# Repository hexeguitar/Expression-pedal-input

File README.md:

# Expression-pedal-input
Work in progress, HW design for an universal expression pedal input

Link to thread at Teensy Forum:
https://forum.pjrc.com/index.php?threads/universal-midi-expression-pedal.76457/

[Html BOM](https://hexeguitar.github.io/Expression-pedal-input/KiCad_project/bom/ExpIn_3_2025-02-24.html "Html BOM")

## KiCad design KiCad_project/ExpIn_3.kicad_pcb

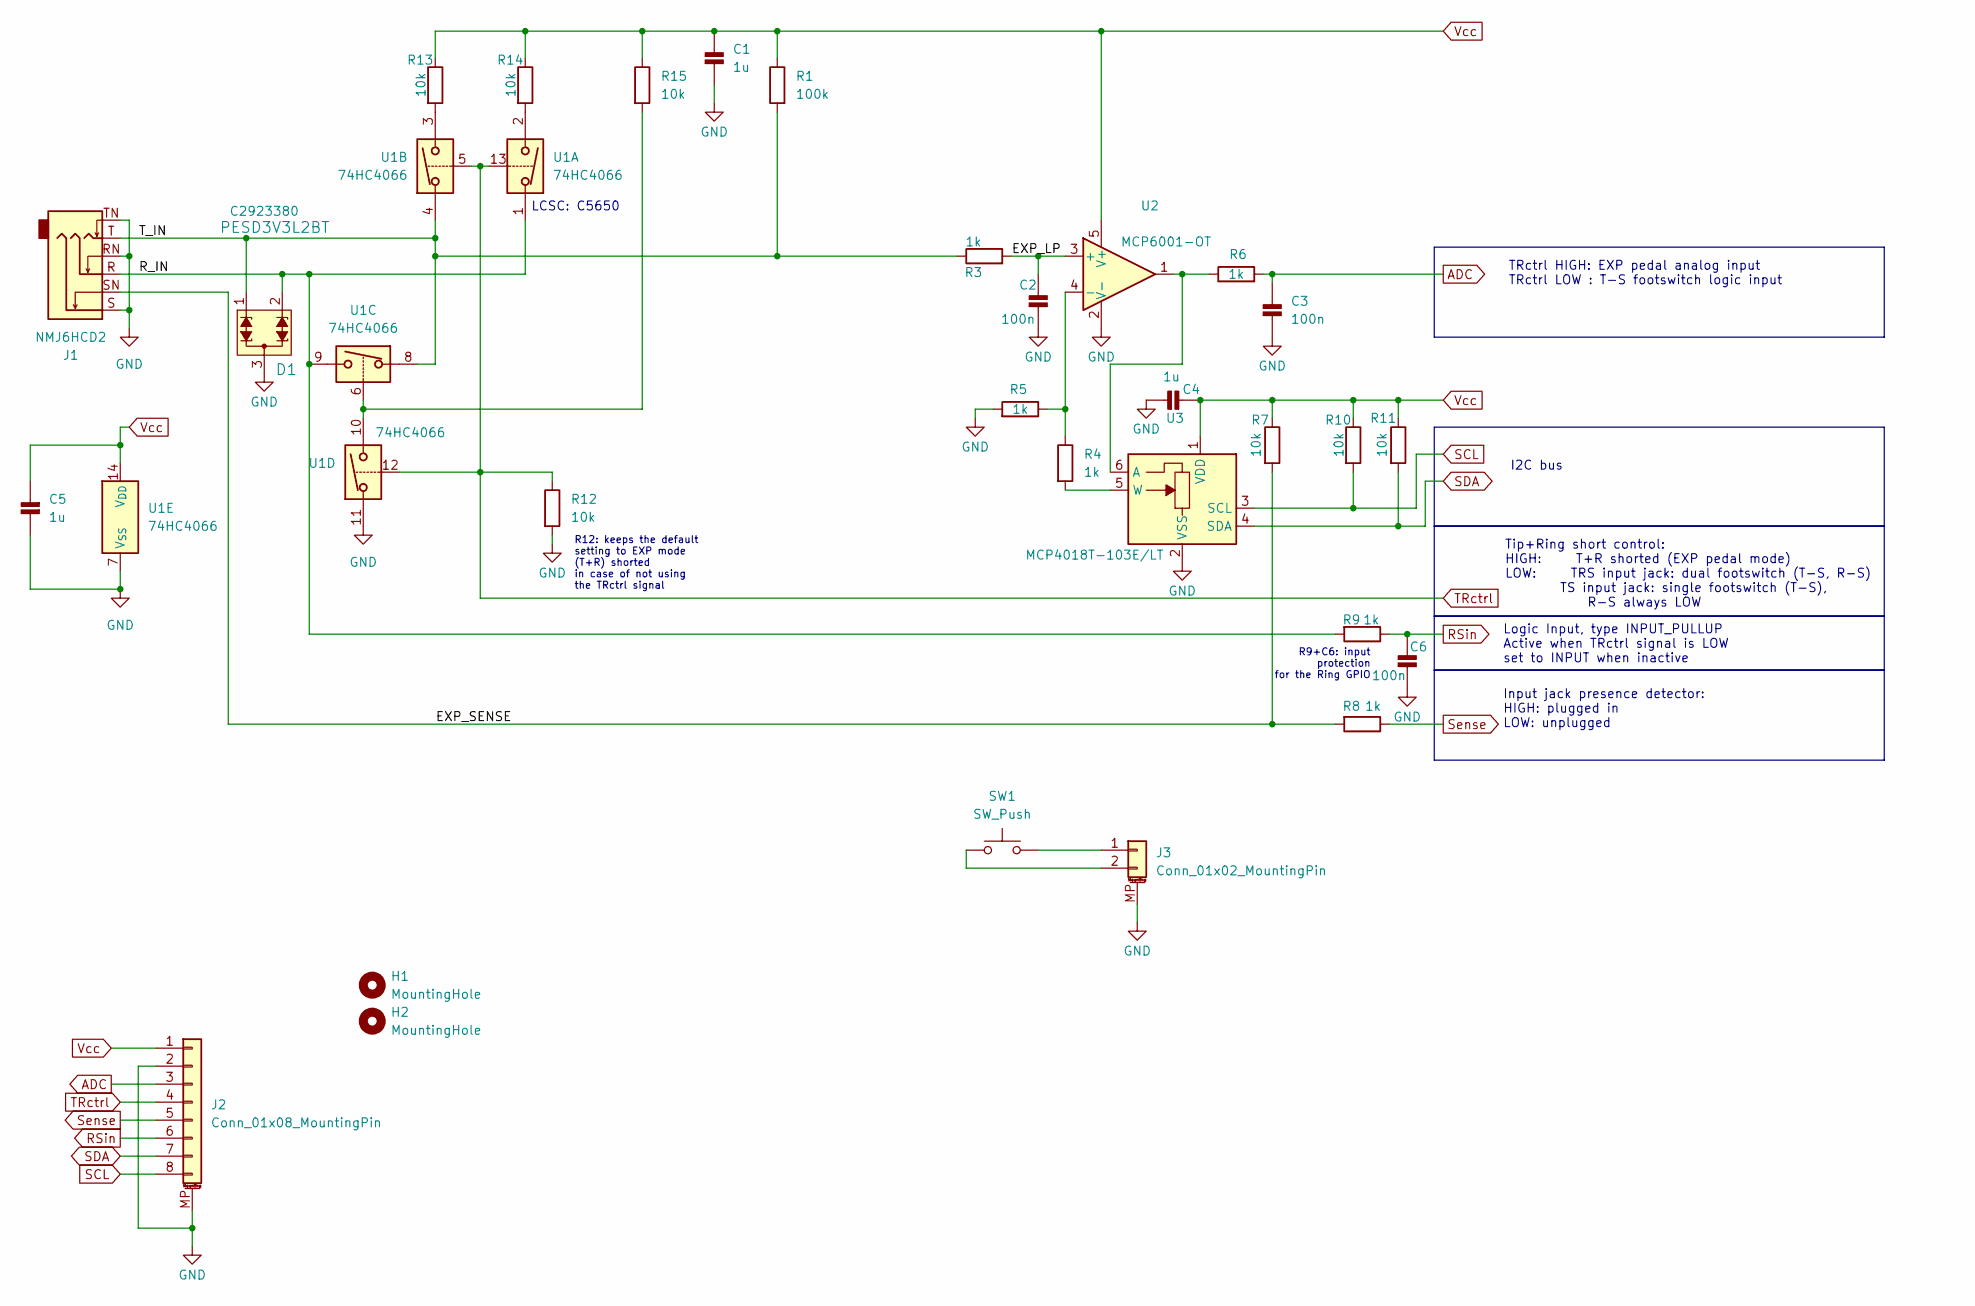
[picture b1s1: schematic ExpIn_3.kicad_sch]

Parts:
C1, C4, C5: 1u; Hx_C_0603_1608Metric
C2, C3, C6: 100n; Hx_C_0603_1608Metric
D1: PESD3V3L2BT; SOT-23; LCSC C2923380
H1, H2: MountingHole; MountingHole_3.2mm_M3
J1: NMJ6HCD2; Jack_6.35mm_Neutrik_NMJ6HCD2_Horizontal
J2: Conn_01x08_MountingPin; JST_SH_BM08B-SRSS-TB_1x08-1MP_P1.00mm_Vertical
J3: Conn_01x02_MountingPin; JST_PH_B2B-PH-SM4-TB_1x02-1MP_P2.00mm_Vertical
R1: 100k; Hx_R_0603_1608Metric
R3, R4, R5, R6, R8, R9: 1k; Hx_R_0603_1608Metric
R7, R10, R11, R12, R13, R14, R15: 10k; Hx_R_0603_1608Metric
SW1: SW_Push; SW_Tactile_SPST_Angled_PTS645Vx83-2LFS
U1: 74HC4066; TSSOP-14_4.4x5mm_P0.65mm
U2: MCP6001-OT; SOT-23-5
U3: MCP4018T-103E/LT; SOT-363_SC-70-6

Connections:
/EXP_LP: C2.1, R3.2, U2.3 (+)
/EXP_SENSE: J1.SN, R7.2, R8.2
/R_IN: D1.2, J1.R, R9.2, U1.1, U1.9
/T_IN: D1.1, J1.T, R1.2, R3.1, U1.4, U1.8
ADC: C3.1, J2.3, R6.2
GND: C1.2, C2.2, C3.2, C4.1, C5.1, C6.2, D1.3, J1.RN, J1.S, J1.TN, J2.2, J2.MP (MountPin), J3.MP (MountPin), R5.2, R12.2, U1.7 (V_{SS}), U1.11, U2.2 (V-), U3.2 (VSS)
unnamed: J3.1, SW1.2
unnamed: J3.2, SW1.1
unnamed: R13.2, U1.3
unnamed: R14.2, U1.2
unnamed: R15.2, U1.6, U1.10
unnamed: R4.1, R5.1, U2.4 (-)
unnamed: R6.1, U2.1, U3.6 (A)
unnamed: R4.2, U3.5 (W)
RSin: C6.1, J2.6, R9.1
SCL: J2.8, R10.2, U3.3 (SCL)
SDA: J2.7, R11.2, U3.4 (SDA)
Sense: J2.5, R8.1
TRctrl: J2.4, R12.1, U1.5, U1.12, U1.13
Vcc: C1.1, C4.2, C5.2, J2.1, R1.1, R7.1, R10.1, R11.1, R13.1, R14.1, R15.1, U1.14 (V_{DD}), U2.5 (V+), U3.1 (VDD)

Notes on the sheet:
LCSC: C5650
Input jack presence detector: HIGH: plugged in LOW: unplugged
I2C bus
R9+C6: input protection for the Ring GPIO
Logic Input, type INPUT_PULLUP Active when TRctrl signal is LOW set to INPUT when inactive
Tip+Ring short control: HIGH: T+R shorted (EXP pedal mode) LOW: TRS input jack: dual footswitch (T-S, R-S) TS input jack: single footswitch (T-S), R-S always LOW
R12: keeps the default setting to EXP mode (T+R) shorted in case of not using the TRctrl signal
TRctrl HIGH: EXP pedal analog input TRctrl LOW : T-S footswitch logic input

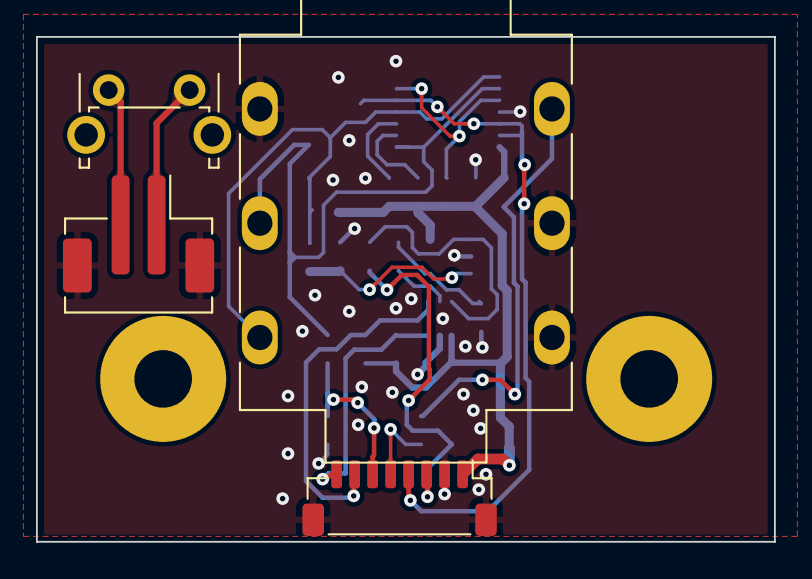
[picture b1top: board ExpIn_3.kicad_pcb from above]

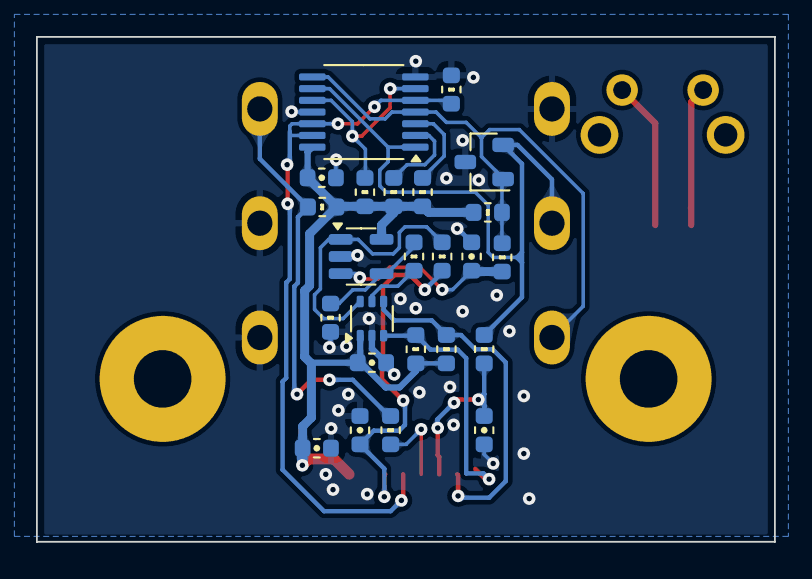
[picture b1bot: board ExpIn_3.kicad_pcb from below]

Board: 2 copper layers, 41.0 x 28.1 mm, 30 parts (24 on the bottom side), 20 nets.

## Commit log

2025-02-20 initial commit - V3
2025-02-24 SMT connectors, gain control
2025-02-24 board size update, dec. caps 1u, bom
2025-02-24 schematic pdf update
2025-02-24 readme update bom link
